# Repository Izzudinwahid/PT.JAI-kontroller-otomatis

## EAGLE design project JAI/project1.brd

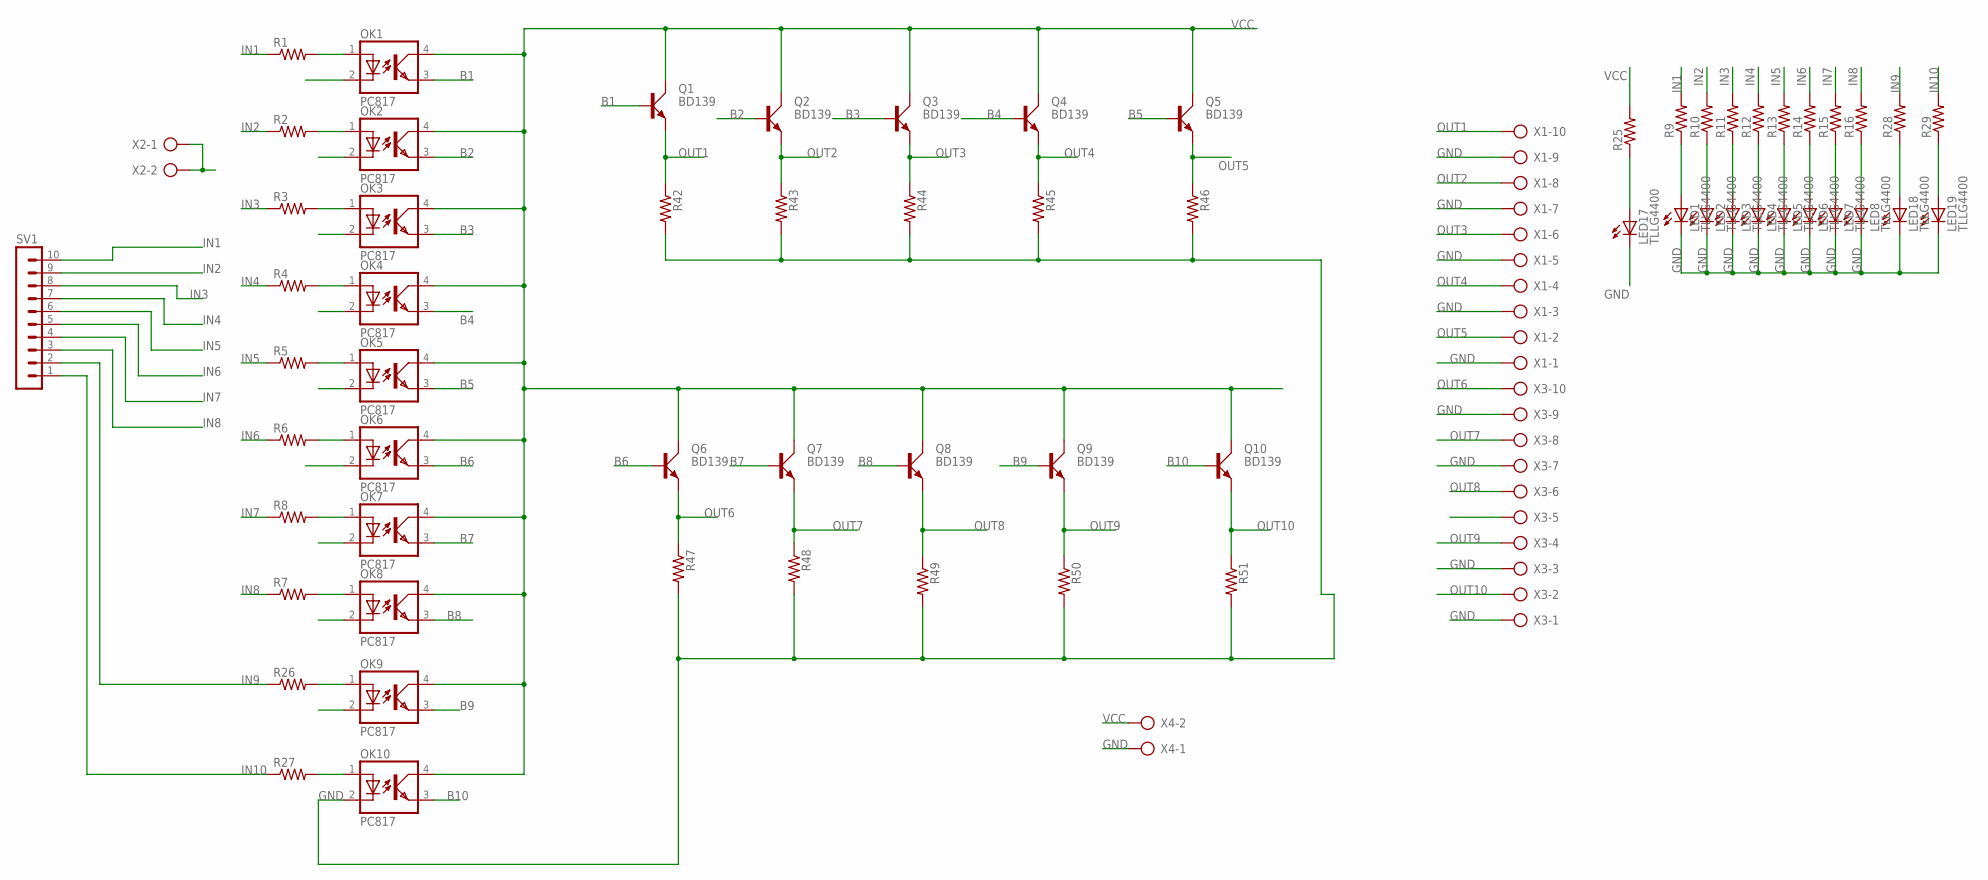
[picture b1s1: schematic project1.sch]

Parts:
LED1, LED2, LED3, LED4, LED5, LED6, LED7, LED8, LED17, LED18, LED19: TLLG4400; LED3MM
OK1, OK2, OK3, OK4, OK5, OK6, OK7, OK8, OK9, OK10: PC817; DIL04
Q1, Q2, Q3, Q4, Q5, Q6, Q7, Q8, Q9, Q10: BD139; TO126AV
R1, R2, R3, R4, R5, R6, R7, R8, R9, R10, R11, R12, R13, R14, R15, R16, R25, R26, R27, R28, R29, R42, R43, R44, R45, R46, R47, R48, R49, R50, R51: R-US_0207/10; 0207/10
SV1: MA10-1
X1, X3: AK300/10
X2, X4: AK300/2

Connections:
B1: OK1.3 (EMIT), Q1.B
B2: OK2.3 (EMIT), Q2.B
B3: OK3.3 (EMIT), Q3.B
B4: OK4.3 (EMIT), Q4.B
B5: OK5.3 (EMIT), Q5.B
B6: OK6.3 (EMIT), Q6.B
B7: OK7.3 (EMIT), Q7.B
B8: OK8.3 (EMIT), Q8.B
B9: OK9.3 (EMIT), Q9.B
B10: OK10.3 (EMIT), Q10.B
GND: LED1.K (C), LED2.K (C), LED3.K (C), LED4.K (C), LED5.K (C), LED6.K (C), LED7.K (C), LED8.K (C), LED17.K (C), LED18.K (C), LED19.K (C), OK1.2 (C), OK2.2 (C), OK3.2 (C), OK4.2 (C), OK5.2 (C), OK6.2 (C), OK7.2 (C), OK8.2 (C), OK9.2 (C), OK10.2 (C), R42.2, R43.2, R44.2, R45.2, R46.2, R47.2, R48.2, R49.2, R50.2, R51.2, X1.1, X1.3, X1.5, X1.7, X1.9, X2.1, X2.2, X3.1, X3.3, X3.5, X3.7, X3.9, X4.1
IN1: R1.1, R9.2, SV1.10
IN2: R2.1, R10.2, SV1.9
IN3: R3.1, R11.2, SV1.8
IN4: R4.1, R12.2, SV1.7
IN5: R5.1, R13.2, SV1.6
IN6: R6.1, R14.2, SV1.5
IN7: R8.1, R15.2, SV1.4
IN8: R7.1, R16.2, SV1.3
IN9: R26.1, R28.2, SV1.2
IN10: R27.1, R29.2, SV1.1
unnamed: OK1.1 (A), R1.2
unnamed: OK2.1 (A), R2.2
unnamed: OK3.1 (A), R3.2
unnamed: OK4.1 (A), R4.2
unnamed: OK5.1 (A), R5.2
unnamed: OK6.1 (A), R6.2
unnamed: OK7.1 (A), R8.2
unnamed: OK8.1 (A), R7.2
unnamed: LED17.A, R25.1
unnamed: OK9.1 (A), R26.2
unnamed: OK10.1 (A), R27.2
unnamed: LED18.A, R28.1
unnamed: LED19.A, R29.1
unnamed: LED1.A, R9.1
unnamed: LED2.A, R10.1
unnamed: LED3.A, R11.1
unnamed: LED4.A, R12.1
unnamed: LED5.A, R13.1
unnamed: LED6.A, R14.1
unnamed: LED7.A, R15.1
unnamed: LED8.A, R16.1
OUT1: Q1.E, R42.1, X1.10
OUT2: Q2.E, R43.1, X1.8
OUT3: Q3.E, R44.1, X1.6
OUT4: Q4.E, R45.1, X1.4
OUT5: Q5.E, R46.1, X1.2
OUT6: Q6.E, R47.1, X3.10
OUT7: Q7.E, R48.1, X3.8
OUT8: Q8.E, R49.1, X3.6
OUT9: Q9.E, R50.1, X3.4
OUT10: Q10.E, R51.1, X3.2
VCC: OK1.4 (COL), OK2.4 (COL), OK3.4 (COL), OK4.4 (COL), OK5.4 (COL), OK6.4 (COL), OK7.4 (COL), OK8.4 (COL), OK9.4 (COL), OK10.4 (COL), Q1.C, Q2.C, Q3.C, Q4.C, Q5.C, Q6.C, Q7.C, Q8.C, Q9.C, Q10.C, R25.2, X4.2

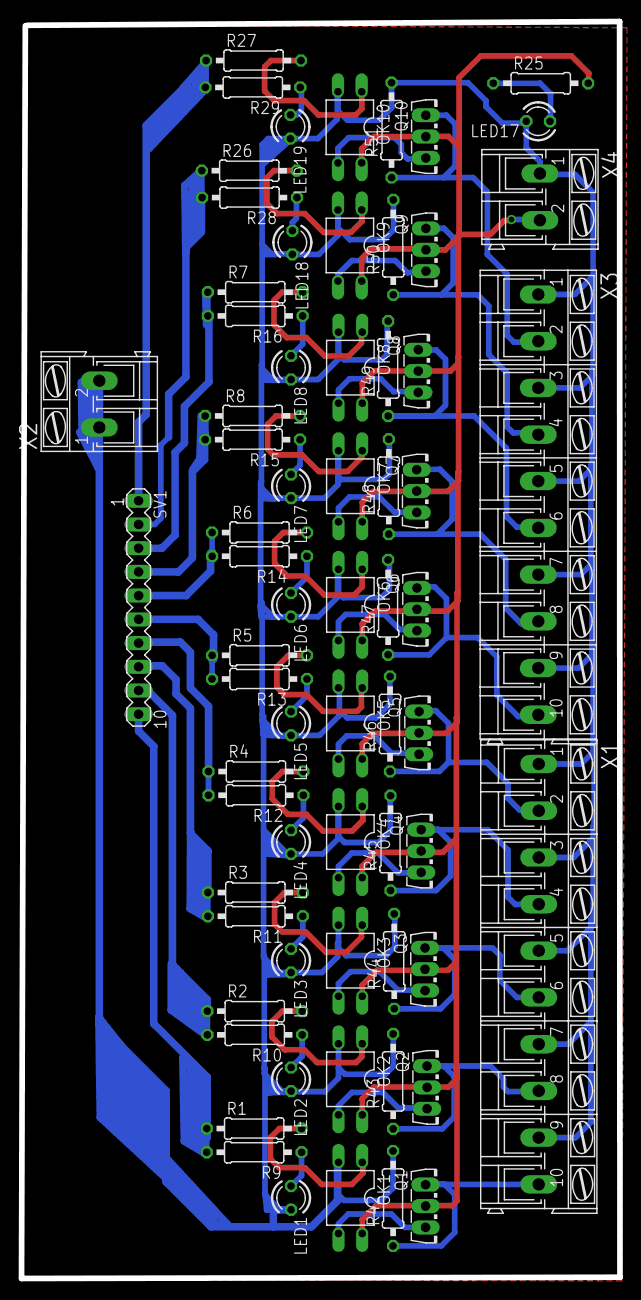
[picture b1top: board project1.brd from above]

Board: 2 copper layers, 64.1 x 134.6 mm, 67 parts (0 on the bottom side), 53 nets.

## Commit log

2023-07-24 PCB fix v1.0
